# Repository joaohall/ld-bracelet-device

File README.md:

<div align="center" id="top"> 

  &#xa0;

  <!-- <a href="https://ldbraceletdevice.netlify.app">Demo</a> -->
</div>

<h1 align="center">Ld Bracelet Device</h1>

<p align="center">

  <!--  -->

  <!--  -->

  <!--  -->
</p>

<Status>

< <h4 align="center"> 
	🚧  Ld Bracelet Device 🚀 Under construction...  🚧
</h4> 

<hr> 

<p align="center">
  <a href="#dart-about">About</a> &#xa0; | &#xa0; 
  <a href="#sparkles-features">Features</a> &#xa0; | &#xa0;
  <a href="#rocket-technologies">Technologies</a> &#xa0; | &#xa0;
  <a href="#white_check_mark-requirements">Requirements</a> &#xa0; | &#xa0;
  <a href="#checkered_flag-starting">Starting</a> &#xa0; | &#xa0;
  <a href="#memo-license">License</a> &#xa0; | &#xa0;
  <a href="https://github.com/{{YOUR_GITHUB_USERNAME}}" target="_blank">Author</a>
</p>

<br>

## :dart: About ##

A open-source bracelet that offers morse code for long distance partner using bluetooth module

## :sparkles: Features ##

:heavy_check_mark: Feature 1;\
:heavy_check_mark: Feature 2;\
:heavy_check_mark: Feature 3;

## :rocket: Technologies ##

The following tools were used in this project:

- [Autodesk Eagle](https://expo.io/)
- [Fusion 360](https://nodejs.org/en/)
- [Blender](https://pt-br.reactjs.org/)
- [AutoCad](https://reactnative.dev/)
- [Arduino IDE](https://www.typescriptlang.org/)

## :white_check_mark: Requirements ##

Before starting :checkered_flag:, you need to have [Git](https://git-scm.com) and [Node](https://nodejs.org/en/) installed.

## :checkered_flag: Starting ##

```bash
# Clone this project
$ git clone https://github.com/{{YOUR_GITHUB_USERNAME}}/ld-bracelet-device

# Access
$ cd ld-bracelet-device

# Install dependencies
$ yarn

# Run the project
$ yarn start

# The server will initialize in the <http://localhost:3000>
```

## :memo: License ##

This project is under license from MIT. For more details, see the [LICENSE](LICENSE.md) file.

Made with :heart: by <a href="https://github.com/{{YOUR_GITHUB_USERNAME}}" target="_blank">{{YOUR_NAME}}</a>

&#xa0;

<a href="#top">Back to top</a>

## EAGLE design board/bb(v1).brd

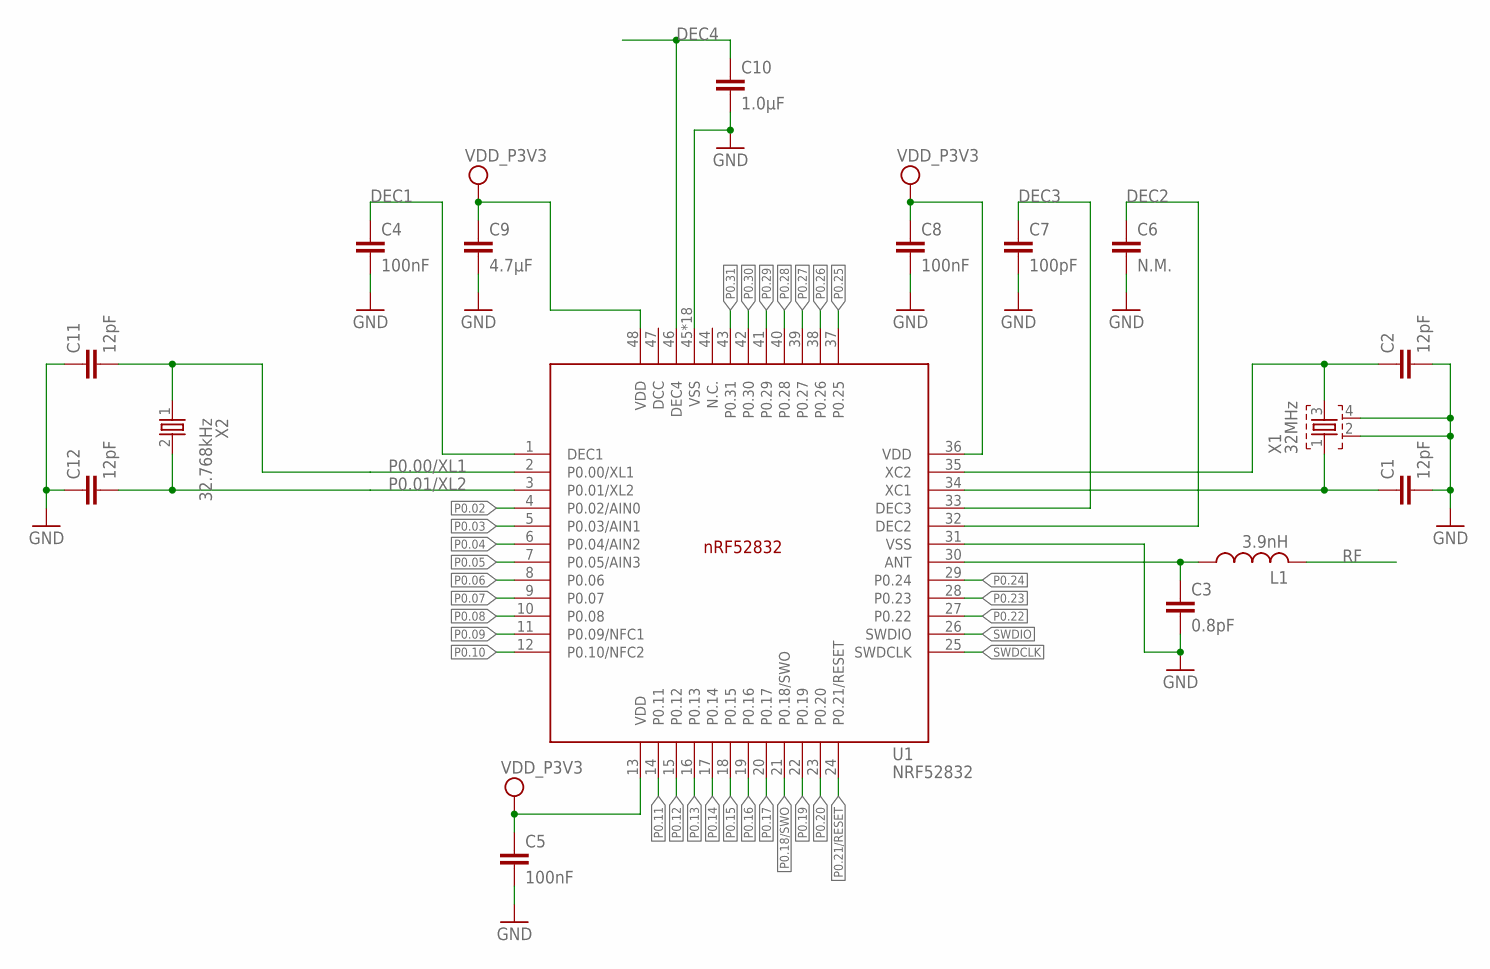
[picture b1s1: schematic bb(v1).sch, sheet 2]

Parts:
C1, C2, C11, C12: 12pF; RESC0402_N
C3: 0.8pF; RESC0402_N
C4, C5, C8: 100nF; RESC0402_N
C6: N.M.; RESC0402_N
C7: 100pF; RESC0402_N
C9: 4.7µF; RESC0603_N
C10: 1.0µF; RESC0603_N
L1: 3.9nH; RESC0402_N
U1: NRF52832; QFN40P600X600X90-48_N
X1: 32MHz; BT-XTAL_2016_N
X2: 32.768kHz; XTAL_3215_N

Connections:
ANT: C3.1, L1.1, U1.30 (ANT)
DEC1: C4.1, U1.1 (DEC1)
DEC2: C6.1, U1.32 (DEC2)
DEC3: C7.1, U1.33 (DEC3)
DEC4: C10.1, U1.46 (DEC4)
GND: C1.2, C2.2, C3.2, C4.2, C5.2, C6.2, C7.2, C8.2, C9.2, C10.2, C11.1, C12.1, U1.31 (VSS), U1.45 (VSS), U1.PAD (VSS), U1.PAD@VIA01 (VSS), U1.PAD@VIA02 (VSS), U1.PAD@VIA03 (VSS), U1.PAD@VIA04 (VSS), U1.PAD@VIA05 (VSS), U1.PAD@VIA06 (VSS), U1.PAD@VIA07 (VSS), U1.PAD@VIA08 (VSS), U1.PAD@VIA09 (VSS), U1.PAD@VIA10 (VSS), U1.PAD@VIA11 (VSS), U1.PAD@VIA12 (VSS), U1.PAD@VIA13 (VSS), U1.PAD@VIA14 (VSS), U1.PAD@VIA15 (VSS), U1.PAD@VIA16 (VSS), X1.2, X1.4
unnamed: C2.1, U1.35 (XC2), X1.3
P0.00/XL1: C11.2, U1.2 (P0.00/XL1), X2.1
P0.01/XL2: C12.2, U1.3 (P0.01/XL2), X2.2
P0.02: U1.4 (P0.02/AIN0)
P0.03: U1.5 (P0.03/AIN1)
P0.04: U1.6 (P0.04/AIN2)
P0.05: U1.7 (P0.05/AIN3)
P0.06: U1.8 (P0.06)
P0.07: U1.9 (P0.07)
P0.08: U1.10 (P0.08)
P0.09: U1.11 (P0.09/NFC1)
P0.10: U1.12 (P0.10/NFC2)
P0.11: U1.14 (P0.11)
P0.12: U1.15 (P0.12)
P0.13: U1.16 (P0.13)
P0.14: U1.17 (P0.14)
P0.15: U1.18 (P0.15)
P0.16: U1.19 (P0.16)
P0.17: U1.20 (P0.17)
P0.18/SWO: U1.21 (P0.18/SWO)
P0.19: U1.22 (P0.19)
P0.20: U1.23 (P0.20)
P0.21/RESET: U1.24 (P0.21/RESET)
P0.22: U1.27 (P0.22)
P0.23: U1.28 (P0.23)
P0.24: U1.29 (P0.24)
P0.25: U1.37 (P0.25)
P0.26: U1.38 (P0.26)
P0.27: U1.39 (P0.27)
P0.28: U1.40 (P0.28)
P0.29: U1.41 (P0.29)
P0.30: U1.42 (P0.30)
P0.31: U1.43 (P0.31)
RF: L1.2
SWDCLK: U1.25 (SWDCLK)
SWDIO: U1.26 (SWDIO)
VDD_P3V3: C5.1, C8.1, C9.1, U1.13 (VDD), U1.36 (VDD), U1.48 (VDD)
X1: C1.1, U1.34 (XC1), X1.1

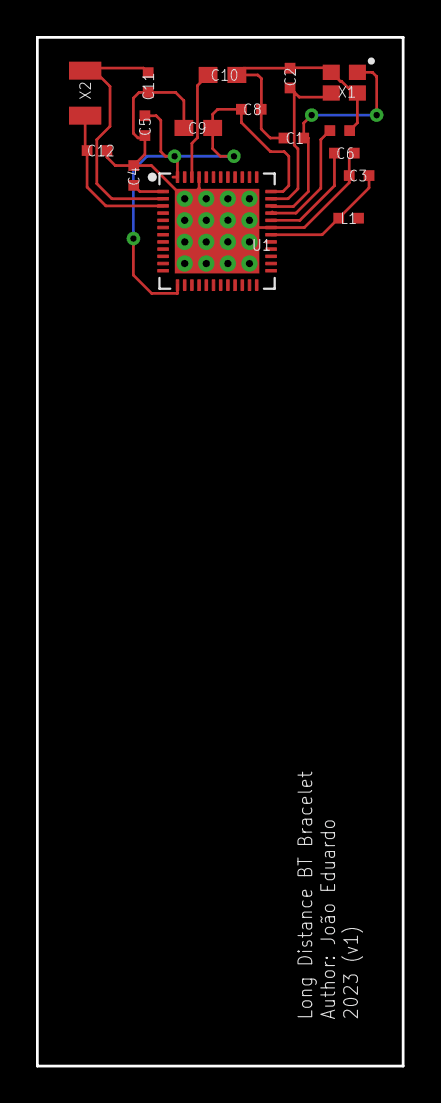
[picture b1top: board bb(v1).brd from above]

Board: 2 copper layers, 20.3 x 57.2 mm, 16 parts (0 on the bottom side), 11 nets.

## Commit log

2023-04-25 Adição da placa
2023-04-25 Adição do módulo bluetooth na placa
